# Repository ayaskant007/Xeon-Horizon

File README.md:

# Xeon Horizon Macropad

The **Xeon Horizon** is a high-performance, 35mm tall programmer's macropad powered by the Seeed Studio XIAO RP2040. It is designed specifically for ultra-fast workflows in code editors, featuring dedicated refactoring/debugging shortcuts, a rotary encoder for rapid code navigation, and a status OLED. 

A unique feature of the Horizon is its upward-facing SK6812 MINI E RGB lighting, which shines directly through hollowed-out text on the top plate to act as an aggressive, high-contrast indicator light.

---

## Project Showcase

[Demo Video](https://youtu.be/cCljSfHtNLw?si=nqkD094vY3MVkHw3)

### The Hackpad

### Case Assembly

### Printed Circuit Board (PCB)

### Schematic

---

## Features & Keymap
* **Controller:** Seeed Studio XIAO RP2040
* **Firmware:** QMK (Direct Pin Matrix, Custom Encoder Map)
* **OLED Display:** SSD1306 (I2C) displaying "XEON HORIZON" and "PROG_MODE" status.
* **Lighting:** 4x SK6812 MINI E LEDs running at maximum brightness for Top-Down hollow text illumination.

### Default Shortcuts:
* **Key 1:** Copy (`Ctrl + C`)
* **Key 2:** Paste (`Ctrl + V`)
* **Key 3:** Undo (`Ctrl + Z`)
* **Key 4:** Run/Debug (`F5`)
* **Key 5:** Execute/Submit (`Enter`)
* **Encoder CW:** Scroll Down (`Mouse Wheel Down`)
* **Encoder CCW:** Scroll Up (`Mouse Wheel Up`)

---

## Bill of Materials (BOM)

| Item | Quantity | Description / Notes |
| :--- | :---: | :--- |
| **Microcontroller** | 1 | Seeed Studio XIAO RP2040 |
| **Switches** | 4 | MX-compatible mechanical switches |
| **Keycaps** | 4 | 1U Keycaps |
| **Rotary Encoder** | 1 | EC11 Rotary Encoder (with push-button) |
| **Encoder Knob** | 1 | Standard encoder knob |
| **Display** | 1 | 0.91" I2C OLED Display (SSD1306) |
| **LEDs** | 4 | SK6812 MINI E RGB LEDs |
| **PCB** | 1 | Custom Xeon Horizon PCB |
| **Case (Top Plate)**| 1 | 3D Printed Top Plate with hollow text (`Top_Plate.STEP`) |
| **Case (Base)** | 1 | 3D Printed 35mm deep base (`Case.STEP`) |
| **Wiring** | ~ | Hookup wire (for hand-wiring components to the XIAO) |

---

## Build & Flash Instructions
1. Assemble the hardware according to the schematic and the 3D CAD designs.
2. Set up your QMK MSYS environment.
3. Copy the `xeon` firmware folder into `qmk_firmware/keyboards/`.
4. Compile the firmware: `qmk compile -kb xeon -km default`
5. Double-tap the reset button on the XIAO RP2040.
6. Drag and drop the generated `.uf2` file into the `RPI-RP2` drive.

---

## Bill of Materials (BOM)

| Name | Purpose | Qty | Total (INR) |
| :--- | :--- | :---: | :---: |
| **3D PRINTED CASE FROM PRINTING LEGION** | For volume control | 1 | 300INR |
| **HACKPAD KIT FROM HACK CLUB** | for getting the components for the pcb | 1 | - |
| **PCB FROM LIONCIRCUITS** | for getting the components for the pcb | 1 | 1200INR |

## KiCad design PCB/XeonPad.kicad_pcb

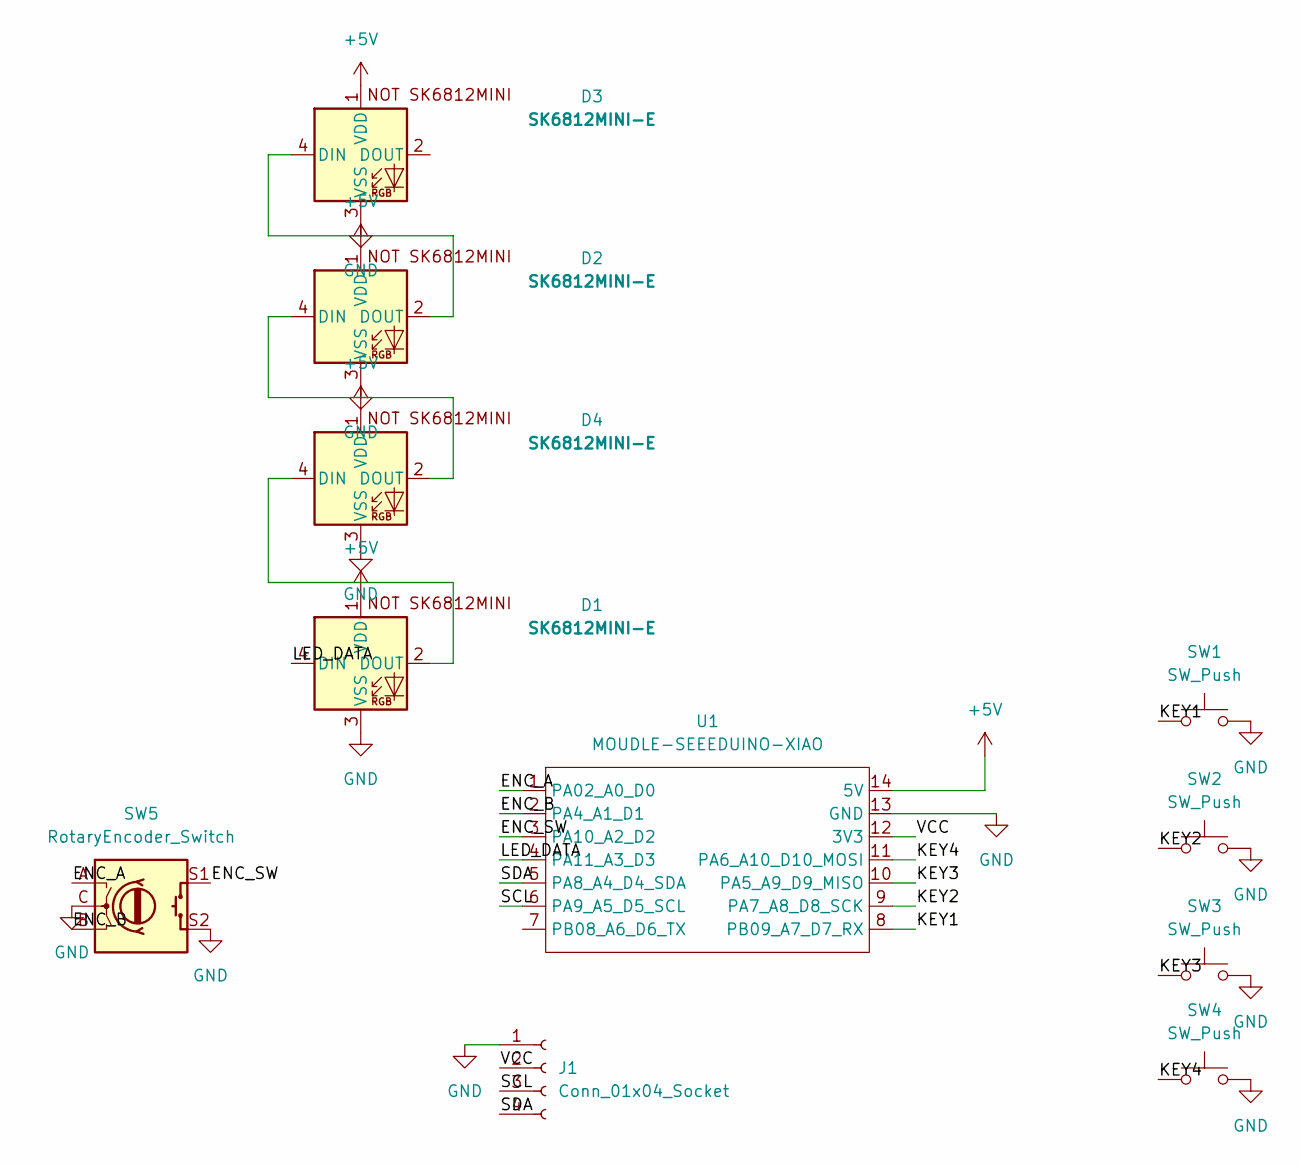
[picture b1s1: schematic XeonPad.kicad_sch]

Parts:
D1, D2, D3, D4: SK6812MINI-E; SK6812MINI-E_fixed
J1: Conn_01x04_Socket; PinHeader_1x04_P2.54mm_Vertical
SW1, SW2, SW3, SW4: SW_Push; SW_Cherry_MX_1.00u_PCB
SW5: RotaryEncoder_Switch; RotaryEncoder_Alps_EC11E-Switch_Vertical_H20mm
U1: MOUDLE-SEEEDUINO-XIAO; XIAO-Generic-Hybrid-14P-2.54-21X17.8MM

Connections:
+5V: D1.1 (VDD), D2.1 (VDD), D3.1 (VDD), D4.1 (VDD), U1.14 (5V)
/ENC_A: SW5.A, U1.1 (PA02_A0_D0)
/ENC_B: SW5.B, U1.2 (PA4_A1_D1)
/ENC_SW: SW5.S1, U1.3 (PA10_A2_D2)
/KEY1: SW1.1, U1.8 (PB09_A7_D7_RX)
/KEY2: SW2.1, U1.9 (PA7_A8_D8_SCK)
/KEY3: SW3.1, U1.10 (PA5_A9_D9_MISO)
/KEY4: SW4.1, U1.11 (PA6_A10_D10_MOSI)
/LED_DATA: D1.4 (DIN), U1.4 (PA11_A3_D3)
/SCL: J1.3, U1.6 (PA9_A5_D5_SCL)
/SDA: J1.4, U1.5 (PA8_A4_D4_SDA)
/VCC: J1.2, U1.12 (3V3)
GND: D1.3 (VSS), D2.3 (VSS), D3.3 (VSS), D4.3 (VSS), J1.1, SW1.2, SW2.2, SW3.2, SW4.2, SW5.C, SW5.S2, U1.13 (GND)
unnamed: D1.2 (DOUT), D4.4 (DIN)
unnamed: D2.4 (DIN), D4.2 (DOUT)
unnamed: D2.2 (DOUT), D3.4 (DIN)

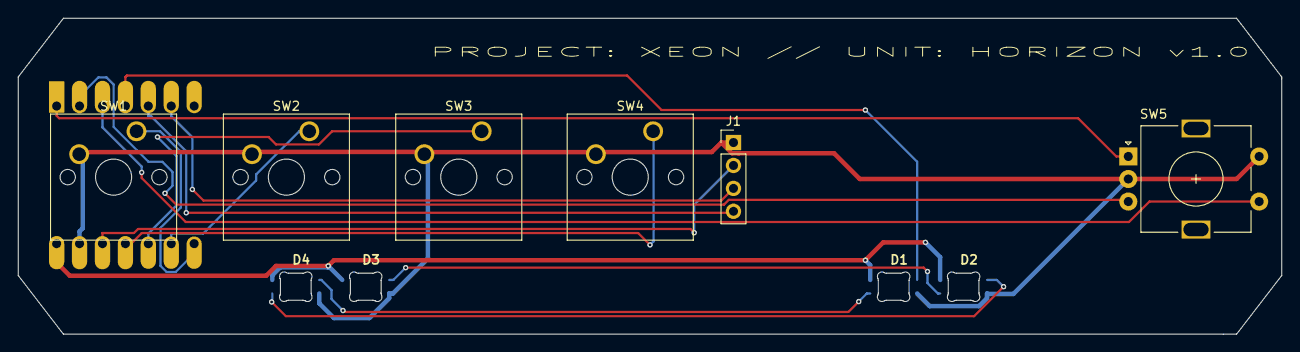
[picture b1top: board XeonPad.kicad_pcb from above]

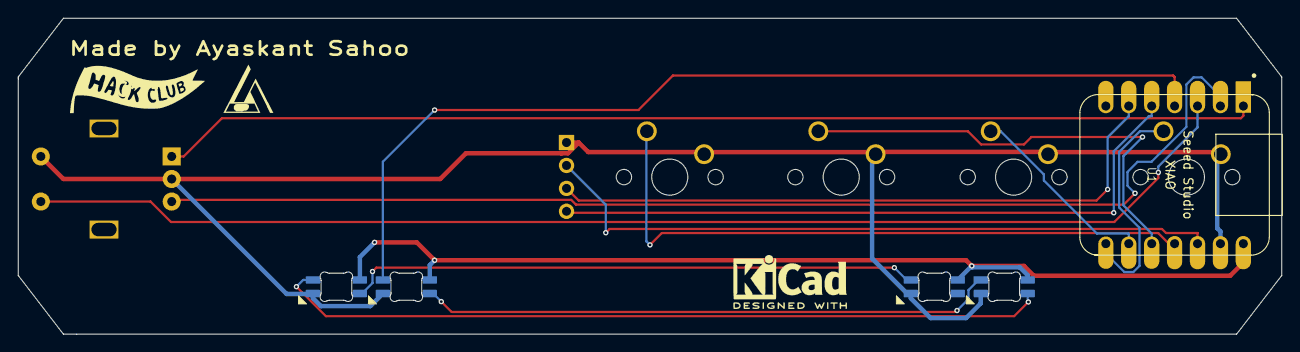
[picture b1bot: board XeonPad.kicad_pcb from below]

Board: 2 copper layers, 139.9 x 35.0 mm, 12 parts (2 on the bottom side), 16 nets.

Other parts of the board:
logo: LOGO; 007

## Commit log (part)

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2026-03-04 Added PCB files and PCB production files
2026-03-04 Added production CAD
2026-03-04 Updated Readme and put the gerbers in a zip
2026-03-04 Fix image links in Project Showcase section
    Updated image links in the Project Showcase section of the README.
2026-03-04 Fix image links in README.md
    Updated image links in the README for Hackpad and PCB Layout.
2026-03-04 Change image URL for Overall Hackpad
    Updated image URL for Overall Hackpad in README.
2026-03-04 Update Hackpad image link in README
2026-03-31 Update image link for Overall Hackpad in README
2026-06-04 Add Bill of Materials section to README
2026-06-04 Add MUSIC/SYS layers, enable RGB, switch I2C
    Introduce new functionality and hardware config updates: add BOM.csv and a board mcuconf.h to enable RP2040 I2C1; switch I2C driver in config.h to I2CD2. Disable OLED support in keyboard.json and rem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
